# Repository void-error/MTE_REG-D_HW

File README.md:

# MTE_REG-D_HW
Voltage regulators for the digital section

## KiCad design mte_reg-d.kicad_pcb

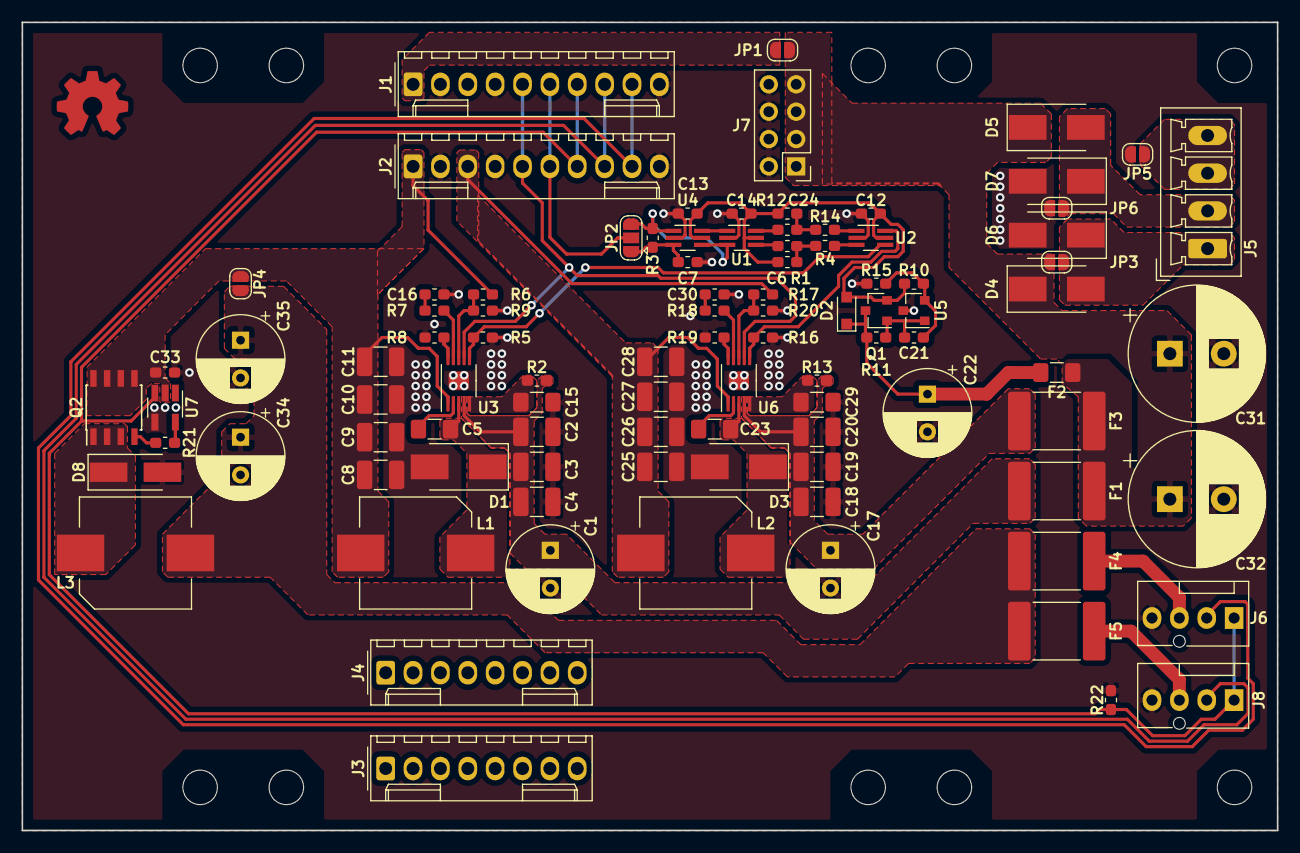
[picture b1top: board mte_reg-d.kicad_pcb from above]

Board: 2 copper layers, 116.5 x 75.0 mm, 107 parts (0 on the bottom side), 57 nets.

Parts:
C1, C17, C22, C34, C35: 33u; CP_Radial_D8.0mm_P3.50mm
C2, C3, C4, C18, C19, C20: 4u7; C_1210_3225Metric_Pad1.42x2.65mm_HandSolder
C5, C15, C23, C29: 470n; C_1206_3216Metric_Pad1.42x1.75mm_HandSolder
C6, C21, C24: 10n; C_0603_1608Metric_Pad1.05x0.95mm_HandSolder
C7: C; C_0603_1608Metric_Pad1.05x0.95mm_HandSolder
C8, C9, C10, C11: 10u; C_1210_3225Metric_Pad1.42x2.65mm_HandSolder
C12, C13, C14, C33: 100n; C_0603_1608Metric_Pad1.05x0.95mm_HandSolder
C16, C30: 680p; C_0603_1608Metric_Pad1.05x0.95mm_HandSolder
C25, C26, C27, C28: 22u; C_1210_3225Metric_Pad1.42x2.65mm_HandSolder
C31, C32: 1000u; CP_Radial_D12.5mm_P5.00mm
D1, D3, D4, D5, D6, D7: SK55; D_SMB_Handsoldering
D2: D; D_SOD-323_HandSoldering
D8: SK35; D_SMA_Handsoldering
F1, F3: SL185-33; Fuse_2920_7451Metric_Pad2.10x5.45mm_HandSolder
F2: SN005-60; Fuse_1206_3216Metric_Pad1.42x1.75mm_HandSolder
F4, F5: SL075-33; Fuse_2920_7451Metric_Pad2.10x5.45mm_HandSolder
J1, J2: Conn_01x10; Molex_KK-254_AE-6410-10A_1x10_P2.54mm_Vertical
J3, J4: Conn_01x08; Molex_KK-254_AE-6410-08A_1x08_P2.54mm_Vertical
J5: Conn_01x04; PhoenixContact_MCV_1,5_4-G-3.5_1x04_P3.50mm_Vertical
J6, J8: Fan Connector; FanPinHeader_1x04_P2.54mm_Vertical
J7: Conn_02x04_Odd_Even; PinHeader_2x04_P2.54mm_Vertical
JP1, JP3, JP4, JP5, JP6: GS2; SolderJumper-2_P1.3mm_Open_RoundedPad1.0x1.5mm
JP2: GS3; SolderJumper-3_P1.3mm_Open_RoundedPad1.0x1.5mm
L1: 10u; L_Wuerth_WE-PDF_Handsoldering
L2: 3u3; L_Wuerth_WE-PDF_Handsoldering
L3: 100u; L_Wuerth_WE-PDF_Handsoldering
LOGO1: OSHW; OSHW-Symbol_6.7x6mm_Copper
MK1, MK2, MK3, MK4, MK5, MK6, MK7, MK8, MK9, MK10: Mounting_Hole; MountingHole_3.2mm_M3
Q1: BC847; SOT-23
Q2: IRF7241; SOIC-8_3.9x4.9mm_P1.27mm
R1, R5, R9, R11, R12, R16, R22: 33k; R_0603_1608Metric_Pad1.05x0.95mm_HandSolder
R2, R13, R18: 15k; R_0603_1608Metric_Pad1.05x0.95mm_HandSolder
R3: R; R_0603_1608Metric_Pad1.05x0.95mm_HandSolder
R4, R14, R21: 100R; R_0603_1608Metric_Pad1.05x0.95mm_HandSolder
R6: 470k; R_0603_1608Metric_Pad1.05x0.95mm_HandSolder
R7: 18k; R_0603_1608Metric_Pad1.05x0.95mm_HandSolder
R8, R19: 120k; R_0603_1608Metric_Pad1.05x0.95mm_HandSolder
R10: 3k3; R_0603_1608Metric_Pad1.05x0.95mm_HandSolder
R15: 10k; R_0603_1608Metric_Pad1.05x0.95mm_HandSolder
R17: 150k; R_0603_1608Metric_Pad1.05x0.95mm_HandSolder
R20: 47k; R_0603_1608Metric_Pad1.05x0.95mm_HandSolder
U1, U2, U4: 74LVC2G14; SOT-363_SC-70-6_Handsoldering
U3, U6: LT3693; MSOP-10-1EP_3x3mm_P0.5mm_EP1.68x1.88mm
U5: TL431DBZ; SOT-23
U7: MCP1415; SOT-23-5_HandSoldering

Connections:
+3V3D: C12.1, C13.1, C14.1, D2.2, Q1.2, R1.1, R10.1, R12.1, U1.5, U2.5, U4.5
+5V0D: C25.1, C26.1, C27.1, C28.1, J1.3, J2.3, L2.2, R17.1, U6.1
+12V: C8.1, C9.1, C10.1, C11.1, C33.1, J1.1, J2.1, JP1.1, JP4.1, L1.2, Q2.5, Q2.6, Q2.7, Q2.8, R6.1, U3.1, U7.2
+V: C31.1, C32.1, D4.1, D5.1, F1.2, F2.1, F3.2, J7.1, J7.3, J7.5, J7.7, JP1.2, JP3.1
/PG: J1.5, J2.5, U3.7, U6.7
/PWM: J1.7, J2.7, J6.1, J8.1, R22.1, U7.3
/RPM0: J1.8, J2.8, J8.2
/RPM1: J1.9, J2.9, J6.2
/SYNC: J1.6, J2.6, JP2.2
DGND: C1.2, C2.2, C3.2, C4.2, C7.2, C8.2, C9.2, C10.2, C11.2, C12.2, C13.2, C14.2, C15.2, C16.2, C17.2, C18.2, C19.2, C20.2, C22.2, C25.2, C26.2, C27.2, C28.2, C29.2, C30.2, C31.2, C32.2, C33.2, C34.2, C35.2, D1.2, D3.2, D6.2, D7.2, D8.2, J1.2, J1.4, J1.10, J2.2, J2.4, J2.10, J6.4, J7.2, J7.4, J7.6, J7.8, J8.4, JP5.2, JP6.2, R5.2, R8.2, R9.1, R15.2, R16.2, R19.2, R20.1, R22.2, U1.2, U2.2, U3.11, U4.2, U5.3, U6.11, U7.4
unnamed: C1.1, C2.1, C3.1, C4.1, F1.1, R2.1, U3.4
unnamed: C5.1, D1.1, L1.1, U3.3
unnamed: C5.2, U3.2
unnamed: C6.1, R1.2, R4.2
unnamed: C6.2, U1.4
unnamed: C7.1, JP2.1, R3.2, U4.3
unnamed: C15.1, R2.2, U3.5
unnamed: C16.1, R7.2
unnamed: C17.1, C18.1, C19.1, C20.1, F3.1, R13.1, U6.4
unnamed: C21.1, R10.2, R15.1, U5.2
unnamed: C21.2, Q1.1, R11.1, U5.1
unnamed: C22.1, D2.1, F2.2, Q1.3, R11.2
unnamed: C23.1, D3.1, L2.1, U6.3
unnamed: C23.2, U6.2
unnamed: C24.1, R12.2, R14.2
unnamed: C24.2, U1.6
unnamed: C29.1, R13.2, U6.5
unnamed: C30.1, R18.2
unnamed: C34.1, C35.1, F4.1, F5.1, JP4.2, L3.2
unnamed: D4.2, D6.1, J5.1, JP3.2
unnamed: D5.2, D7.1, J5.2, JP6.1
unnamed: D8.1, L3.1, Q2.1, Q2.2, Q2.3
unnamed: F4.2, J6.3
unnamed: F5.2, J8.3
unnamed: J3.1, J4.1
unnamed: J3.2, J4.2
unnamed: J3.3, J4.3
unnamed: J3.4, J4.4
unnamed: J3.5, J4.5
unnamed: J3.6, J4.6
unnamed: J3.7, J4.7
unnamed: J3.8, J4.8
unnamed: J5.3, J5.4, JP5.1
unnamed: JP2.3, R3.1, U1.3, U4.1, U4.4
unnamed: Q2.4, R21.2
unnamed: R4.1, U2.3
unnamed: R5.1, U2.4, U3.6
unnamed: R6.2, R9.2, U3.8
unnamed: R7.1, U3.9
unnamed: R8.1, U3.10
unnamed: R14.1, U2.1
unnamed: R16.1, U2.6, U6.6
unnamed: R17.2, R20.2, U6.8
unnamed: R18.1, U6.9
unnamed: R19.1, U6.10
unnamed: R21.1, U7.5
unnamed: U1.1, U4.6

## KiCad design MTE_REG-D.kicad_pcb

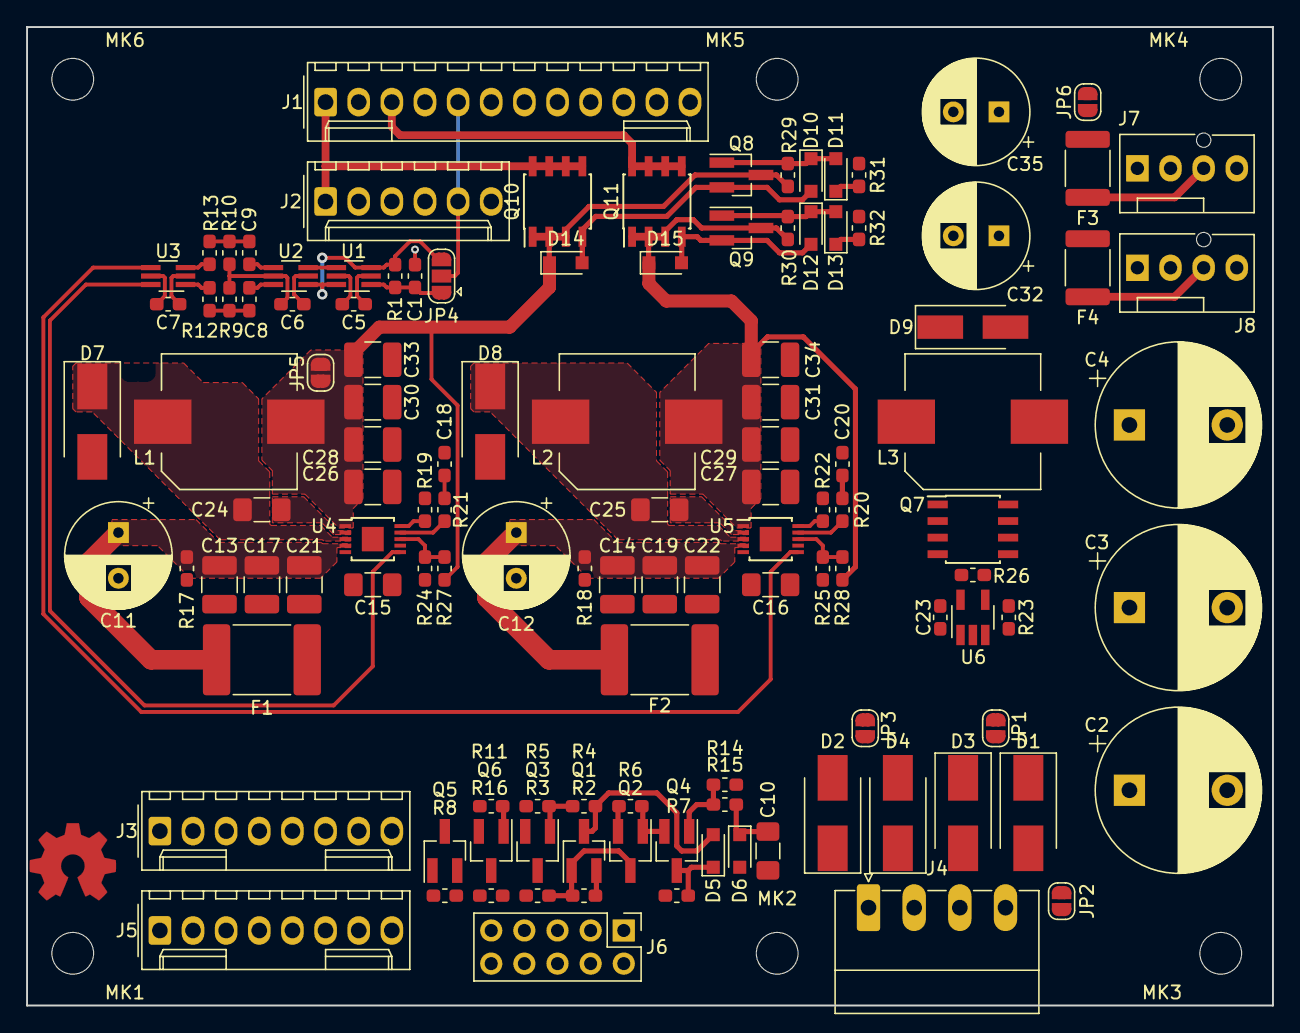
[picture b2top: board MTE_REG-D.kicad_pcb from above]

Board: 2 copper layers, 95.5 x 75.0 mm, 127 parts (0 on the bottom side), 72 nets.

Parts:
C1: C; C_0603_1608Metric_Pad1.05x0.95mm_HandSolder
C2, C3, C4: 1000u; CP_Radial_D12.5mm_P7.50mm
C5, C6, C7, C23: 100n; C_0603_1608Metric_Pad1.05x0.95mm_HandSolder
C8, C9: 10n; C_0603_1608Metric_Pad1.05x0.95mm_HandSolder
C10: 2u2; C_1206_3216Metric_Pad1.42x1.75mm_HandSolder
C11, C12, C32, C35: 33u; CP_Radial_D8.0mm_P3.50mm
C13, C14, C17, C19, C21, C22: 4u7; C_1210_3225Metric_Pad1.42x2.65mm_HandSolder
C15, C16, C24, C25: 470n; C_1206_3216Metric_Pad1.42x1.75mm_HandSolder
C18, C20: 680p; C_0603_1608Metric_Pad1.05x0.95mm_HandSolder
C26, C28, C30, C33: 10u; C_1210_3225Metric_Pad1.42x2.65mm_HandSolder
C27, C29, C31, C34: 22u; C_1210_3225Metric_Pad1.42x2.65mm_HandSolder
D1, D2, D3, D4, D7, D8: SK55; D_SMB_Handsoldering
D5, D6, D10, D11, D12, D13: BAS316; D_SOD-323_HandSoldering
D9: SK35; D_SMA_Handsoldering
D14, D15: MM3Z10; D_SOD-323_HandSoldering
F1: SL125-33; Fuse_2920_7451Metric_Pad2.10x5.45mm_HandSolder
F2: SL075-33; Fuse_2920_7451Metric_Pad2.10x5.45mm_HandSolder
F3, F4: SD075-16; Fuse_1812_4532Metric_Pad1.30x3.40mm_HandSolder
J1: Conn_01x12; Molex_KK-254_AE-6410-12A_1x12_P2.54mm_Vertical
J2: Conn_01x06; Molex_KK-254_AE-6410-06A_1x06_P2.54mm_Vertical
J3, J5: Conn_01x08; Molex_KK-254_AE-6410-08A_1x08_P2.54mm_Vertical
J4: Conn_01x04; PhoenixContact_MC_1,5_4-G-3.5_1x04_P3.50mm_Horizontal
J6: Conn_02x05_Odd_Even; PinHeader_2x05_P2.54mm_Vertical
J7, J8: Fan Connector; FanPinHeader_1x04_P2.54mm_Vertical
JP1, JP2, JP3, JP5, JP6: GS2; SolderJumper-2_P1.3mm_Open_RoundedPad1.0x1.5mm
JP4: GS3; SolderJumper-3_P1.3mm_Open_RoundedPad1.0x1.5mm
L1: 10u; L_Wuerth_WE-PDF_Handsoldering
L2: 3u3; L_Wuerth_WE-PDF_Handsoldering
L3: 100u; L_Wuerth_WE-PDF_Handsoldering
LOGO1: OSHW; OSHW-Symbol_6.7x6mm_Copper
MK1, MK2, MK3, MK4, MK5, MK6: Mounting_Hole; MountingHole_3.2mm_M3
Q1, Q5, Q6, Q8, Q9: BC847; SOT-23_Handsoldering
Q2, Q3, Q4: BC857; SOT-23_Handsoldering
Q7, Q10, Q11: IRF7241; SOIC-8_3.9x4.9mm_P1.27mm
R1: R; R_0603_1608Metric_Pad1.05x0.95mm_HandSolder
R2, R3, R4, R5, R7, R8, R9, R10, R11, R15, R16, R23, R24: 33k; R_0603_1608Metric_Pad1.05x0.95mm_HandSolder
R6: 7k5; R_0603_1608Metric_Pad1.05x0.95mm_HandSolder
R12, R13, R26: 100R; R_0603_1608Metric_Pad1.05x0.95mm_HandSolder
R14: 270k; R_0603_1608Metric_Pad1.05x0.95mm_HandSolder
R17, R18, R20: 15k; R_0603_1608Metric_Pad1.05x0.95mm_HandSolder
R19: 18k; R_0603_1608Metric_Pad1.05x0.95mm_HandSolder
R21, R22: 120k; R_0603_1608Metric_Pad1.05x0.95mm_HandSolder
R25: 47k; R_0603_1608Metric_Pad1.05x0.95mm_HandSolder
R27: 470k; R_0603_1608Metric_Pad1.05x0.95mm_HandSolder
R28: 150k; R_0603_1608Metric_Pad1.05x0.95mm_HandSolder
R29, R30, R31, R32: 3k6; R_0603_1608Metric_Pad1.05x0.95mm_HandSolder
U1, U2, U3: 74LVC2G14; SOT-363_SC-70-6_Handsoldering
U4, U5: LT3693; MSOP-10-1EP_3x3mm_P0.5mm_EP1.68x1.88mm
U6: MCP1415; SOT-23-5_HandSoldering

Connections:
+3V3D: C5.1, C6.1, C7.1, R9.1, R10.1, U1.5, U2.5, U3.5
+5V0D: J1.3, J2.3, Q11.5, Q11.6, Q11.7, Q11.8
+12V: C23.1, J1.1, J2.1, JP6.2, Q7.5, Q7.6, Q7.7, Q7.8, Q10.5, Q10.6, Q10.7, Q10.8, U6.2
+V: C2.1, C3.1, C4.1, D1.1, D3.1, F1.1, F2.2, J6.1, J6.3, J6.5, JP1.1, Q2.2, Q3.2, R2.1, R6.1, R11.1, R14.1, R16.1
/PG: J6.7, Q1.3, R3.2, U4.7, U5.7
/PWM: J1.7, J7.1, J8.1, R23.1, U6.3
/RPM0: J1.9, J8.2
/RPM1: J1.11, J7.2
/SD: J6.9, Q6.3, R16.2, R31.1, R32.1
/SYNC: J1.5, J2.5, JP4.2
DGND: C1.2, C2.2, C3.2, C4.2, C5.2, C6.2, C7.2, C10.2, C11.2, C12.2, C13.2, C14.2, C15.2, C16.2, C17.2, C18.2, C19.2, C20.2, C21.2, C22.2, C23.2, C26.2, C27.2, C28.2, C29.2, C30.2, C31.2, C32.2, C33.2, C34.2, C35.2, D2.2, D4.2, D6.2, D7.2, D8.2, D9.2, J1.2, J1.4, J1.6, J1.8, J1.10, J1.12, J2.2, J2.4, J2.6, J6.2, J6.4, J6.6, J6.8, J6.10, J7.4, J8.4, JP2.2, JP3.2, Q1.2, Q5.2, Q6.2, R5.2, R8.2, R21.2, R22.2, R23.2, R24.1, R25.1, U1.2, U2.2, U3.2, U4.11, U5.11, U6.4
unnamed: C1.1, JP4.1, R1.2, U1.1
unnamed: C8.1, R9.2, R12.2
unnamed: C8.2, U2.6
unnamed: C9.1, R10.2, R13.2
unnamed: C9.2, U2.4
unnamed: C10.1, D6.1, R15.2
unnamed: C11.1, C13.1, C17.1, C21.1, F1.2, JP5.2, R17.1, U4.4
unnamed: C12.1, C14.1, C19.1, C22.1, F2.1, R18.1, U5.4
unnamed: C15.1, R17.2, U4.5
unnamed: C16.1, R18.2, U5.5
unnamed: C18.1, R19.2
unnamed: C20.1, R20.2
unnamed: C24.1, D7.1, L1.1, U4.3
unnamed: C24.2, U4.2
unnamed: C25.1, D8.1, L2.1, U5.3
unnamed: C25.2, U5.2
unnamed: C26.1, C28.1, C30.1, C33.1, D14.1, JP5.1, L1.2, Q8.3, Q10.1, Q10.2, Q10.3, R27.1, R29.2, U4.1
unnamed: C27.1, C29.1, C31.1, C34.1, D15.1, L2.2, Q9.3, Q11.1, Q11.2, Q11.3, R28.1, R30.2, U5.1
unnamed: C32.1, C35.1, F3.1, F4.1, JP6.1, L3.2
unnamed: D1.2, D2.1, J4.1, JP1.2
unnamed: D3.2, D4.1, J4.2, JP3.1
unnamed: D5.1, Q4.3, R7.2
unnamed: D5.2, Q3.3, R4.1
unnamed: D9.1, L3.1, Q7.1, Q7.2, Q7.3
unnamed: D10.1, D11.2, Q8.1, R29.1
unnamed: D10.2, D14.2, Q8.2, Q10.4
unnamed: D11.1, R31.2
unnamed: D12.1, D13.2, Q9.1, R30.1
unnamed: D12.2, D15.2, Q9.2, Q11.4
unnamed: D13.1, R32.2
unnamed: F3.2, J7.3
unnamed: F4.2, J8.3
unnamed: J3.1, J5.1
unnamed: J3.2, J5.2
unnamed: J3.3, J5.3
unnamed: J3.4, J5.4
unnamed: J3.5, J5.5
unnamed: J3.6, J5.6
unnamed: J3.7, J5.7
unnamed: J3.8, J5.8
unnamed: J4.3, J4.4, JP2.1
unnamed: JP4.3, R1.1, U1.3, U1.6, U2.1
unnamed: Q1.1, R4.2, R5.1
unnamed: Q2.1, Q4.2, R6.2
unnamed: Q2.3, Q3.1, R2.2, R3.1
unnamed: Q4.1, R14.2, R15.1
unnamed: Q5.1, R7.1, R8.1
unnamed: Q5.3, Q6.1, R11.2
unnamed: Q7.4, R26.2
unnamed: R12.1, U3.1
unnamed: R13.1, U3.3
unnamed: R19.1, U4.9
unnamed: R20.1, U5.9
unnamed: R21.1, U4.10
unnamed: R22.1, U5.10
unnamed: R24.2, R27.2, U4.8
unnamed: R25.2, R28.2, U5.8
unnamed: R26.1, U6.5
unnamed: U1.4, U2.3
unnamed: U3.4, U5.6
unnamed: U3.6, U4.6

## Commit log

2018-02-27 Added KiCad project files, pdf schematic and license
2018-11-25 Renamed stuff, updated custom libraries
2018-11-25 Updated PDF
2019-12-27 Revised schematic, initial PCB layout complete
2019-12-27 Fixed library references
2020-01-09 Fixed library name

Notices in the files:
mte_reg-d.kicad_pcb:
License: TAPR Open Hardware License - https://www.tapr.org/ohl
